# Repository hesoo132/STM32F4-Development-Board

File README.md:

## 📑 Table of Contents
1. [Power](#1-power-전원부)  
2. [Pin Port](#2-pin-port-핀-포트)  
3. [USB](#3-usb)  
4. [Crystal](#4-crystal-크리스탈-오실레이터)  
5. [MCU](#5-mcu-마이크로컨트롤러-유닛)  
6. [Conclusion](#6-결론)  

---

## 1. Power

- **Function**: Converts external 5V input into a regulated 3.3V supply for the MCU and peripherals.  
- **Components**:  
  - AMS1117 regulator (J1)  
  - Power LED (POW_LED_1) with resistor (330Ω)  
  - Slide switch (SW_Slide_DPDT, SW1) for power control  
  - Decoupling capacitors (0.1µF, 10µF) for stability  

---

## 2. Pin Port

- **Function**: Exposes STM32F407VETx GPIOs through external connectors (J3, J4, J5).  
- **Available Pins**:  
  - GPIO groups: PA, PB, PC, PD, PE  
  - Clock pins: OSC_IN, OSC_OUT, OSC32_IN, OSC32_OUT  
  - Reset and Boot pins  
- **Purpose**: Enables flexible interfacing with sensors, actuators, or other controllers.  

---

## 3. USB

- **Function**: Provides USB communication via a Mini-B connector (J2).  
- **Components**:  
  - MIC2025-1YM USB power switch (U1)  
  - Data lines: USB_DP, USB_DM  
  - Protection & series resistors (22Ω)  
  - Power LED (POW_LED2)  
- **Notes**: Supports regulated USB 5V input, current limiting, and device connectivity.  

---

## 4. Crystal

- **Function**: Provides accurate clock sources for the MCU.  
- **Components**:  
  - 8MHz main oscillator (X1) with load capacitors (20pF)  
  - 32.768kHz RTC crystal (Y1) with 6pF capacitors  
  - BOOT Mode selector (J10)  
  - Reset switch (SW2)  
  - 20-pin JTAG/SWD connector (J12) for debugging  

---

## 5. MCU

- **Model**: STM32F407VETx (ARM Cortex-M4)  
- **Function**: Central controller handling all peripherals and system logic.  
- **Connections**:  
  - VCAP capacitors (2.2µF each)  
  - Power pins (3.3V, GND)  
  - BOOT mode jumper (J11)  
  - VBAT connections (J19, J20, J21)  
  - GPIOs (Ports A–E) routed to external headers  
- **Features**:  
  - High-performance MCU core for DSP and control  
  - Rich GPIO set for flexible interfacing  
  - Supports external oscillators and USB  

---

## 6. Conclusion

The **STM32F4Core board** is a versatile core board designed around the STM32F407VETx MCU.  

- **Power Management**: 5V input regulated to 3.3V, with onboard monitoring LEDs and USB power switch.  
- **Expansion**: GPIO-rich design with external pin headers (J3, J4, J5).  
- **USB Support**: Integrated Mini-B port with MIC2025-based power management.  
- **Clock Accuracy**: Dual-crystal design (8MHz + 32.768kHz) ensures reliable MCU timing.  
- **Debugging**: JTAG/SWD interface available for firmware development.  

This makes the board suitable for **embedded system prototyping, robotics, sensor interfacing, and educational use cases** requiring a stable STM32F4 platform.  

---

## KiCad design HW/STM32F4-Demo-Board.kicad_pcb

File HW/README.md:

# STM32F4Core Hardware Design

## 🔎 Overview
The **STM32F4Core Board** is a custom core platform built on the **STM32F407VETx** MCU.  
It provides stable power regulation, rich GPIO breakouts, USB connectivity, accurate system/RTC clocks, and full JTAG/SWD debug support for embedded development.

---

## 📸 PCB Overview
| Top View | Bottom View |
|----------|-------------|
|  |  |

---

## 📑 Design Resources
- **Schematics**: [STM32F4Core.pdf](STM32F4-Demo-Board.pdf) (6-page schematic for quick view)  
- **EDA Tool**: KiCad (v7)  

---

## 🔧 Key Hardware Notes
- **MCU**: STM32F407VETx (ARM Cortex-M4, 168 MHz, FPU)  
- **Power**: 5 V input → AMS1117 regulator → 3.3 V rail, with on/off slide switch & LED indicator  
- **Clocks**: 8 MHz main crystal + 32.768 kHz RTC crystal  
- **USB**: USB Mini-B connector with **MIC2025-1YM** power switch  
- **GPIO**: PA–PE group pins exposed to headers (J3/J4/J5)  
- **Debug**: 20-pin JTAG header (J12), boot-mode jumper (J11), reset switch (SW2)  

---

## 🧩 Schematic Highlights

### 1) Power
  
- **Regulator**: AMS1117 (5 V → 3.3 V)  
- **Indicators**: Power LED (POW_LED_1)  
- **Switch**: Slide switch (SW_Slide_DPDT) for on/off control  

### 2) Pin Ports
  
- **Headers**: J3, J4, J5  
- **Signals**: MCU GPIO (PA/PB/PC/PD/PE), reset, oscillator pins  
- **Use**: Sensor/actuator connections, external module interfacing  

### 3) USB
  
- **Connector**: USB Mini-B (J2)  
- **Power Switch**: MIC2025-1YM, with EN/FLG signals to MCU  
- **Signals**: Provides regulated **USB_5V** rail (with current-limit & flag)  
- **Note**: **Power-only design** — no D+/D− data lines connected to MCU. 

### 4) Clocks & Debug
  
- **Crystals**: 8 MHz (system), 32.768 kHz (RTC)  
- **Reset**: Push switch (SW2)  
- **Debug**: 20-pin JTAG header (J12)  

### 5) MCU
  
- **Chip**: STM32F407VETx  
- **Support**: VCAP capacitors, bypass network, boot-mode jumper (J11)  
- **Role**: Main controller for application logic & peripherals  

---

## ✅ Progress
- [x] Schematics completed (6 pages)  
- [x] PCB prototype fabricated (Rev. A)  
- [x] Power rails validated (5 V → 3.3 V)  
- [x] JTAG/SWD debug verified   
- [x] Full GPIO validation in progress

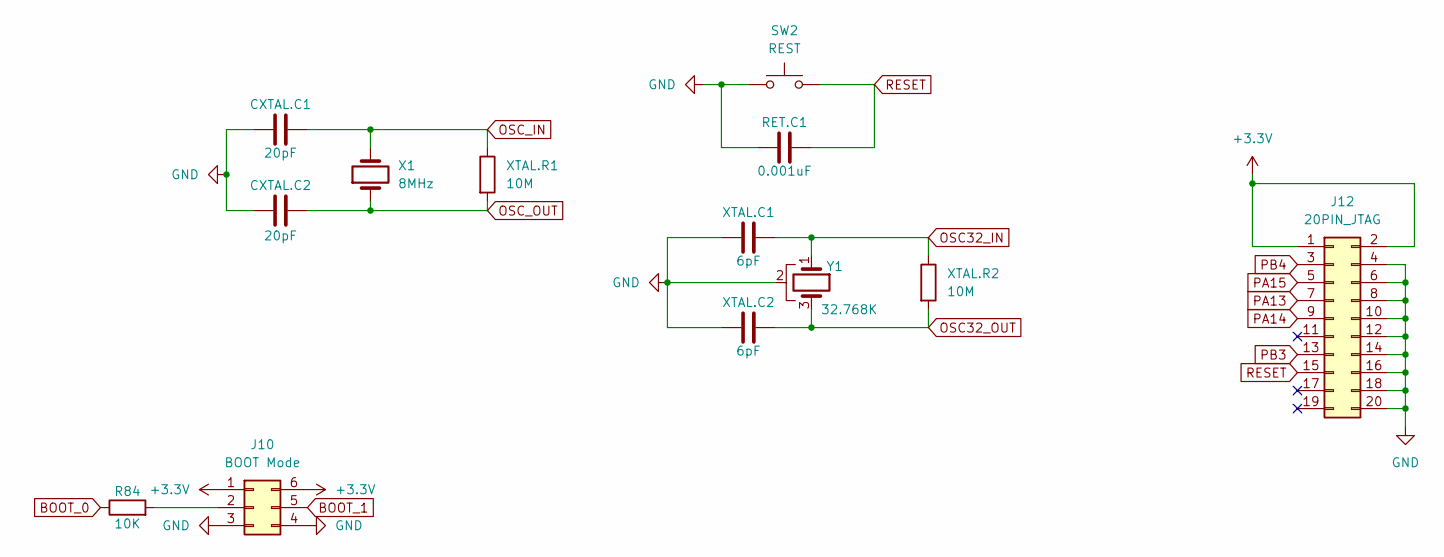
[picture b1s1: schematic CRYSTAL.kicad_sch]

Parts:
CXTAL.C1, CXTAL.C2: 20pF; C_0805_2012Metric
J10: BOOT Mode; PinSocket_2x03_P2.54mm_Vertical
J12: 20PIN_JTAG; IDC-Header_2x10_P2.54mm_Vertical
R84: 10K; C_0805_2012Metric
RET.C1: 0.001uF; C_0805_2012Metric
SW2: REST; SW_MEC_5GSH9
X1: 8MHz; Crystal_HC18-U_Vertical
XTAL.C1, XTAL.C2: 6pF; C_0805_2012Metric
XTAL.R1, XTAL.R2: 10M; R_0805_2012Metric
Y1: 32.768K; Crystal_SMD_MicroCrystal_MS3V-T1R

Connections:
+3.3V: J10.1, J10.6, J12.1, J12.2; also elsewhere on the board
BOOT_0: R84.1; also elsewhere on the board
BOOT_1: J10.5; also elsewhere on the board
GND: CXTAL.C1.1, CXTAL.C2.1, J10.3, J10.4, J12.4, J12.6, J12.8, J12.10, J12.12, J12.14, J12.16, J12.18, J12.20, RET.C1.1, SW2.1 (A), SW2.2 (A), XTAL.C1.1, XTAL.C2.1, Y1.2; also elsewhere on the board
unnamed: J10.2, R84.2
OSC32_IN: XTAL.C1.2, XTAL.R2.1, Y1.1; also elsewhere on the board
OSC32_OUT: XTAL.C2.2, XTAL.R2.2, Y1.3; also elsewhere on the board
OSC_IN: CXTAL.C1.2, X1.2, XTAL.R1.1; also elsewhere on the board
OSC_OUT: CXTAL.C2.2, X1.1, XTAL.R1.2; also elsewhere on the board
PA13: J12.7; also elsewhere on the board
PA14: J12.9; also elsewhere on the board
PA15: J12.5; also elsewhere on the board
PB3: J12.13; also elsewhere on the board
PB4: J12.3; also elsewhere on the board
RESET: J12.15, RET.C1.2, SW2.3 (B), SW2.4 (B); also elsewhere on the board

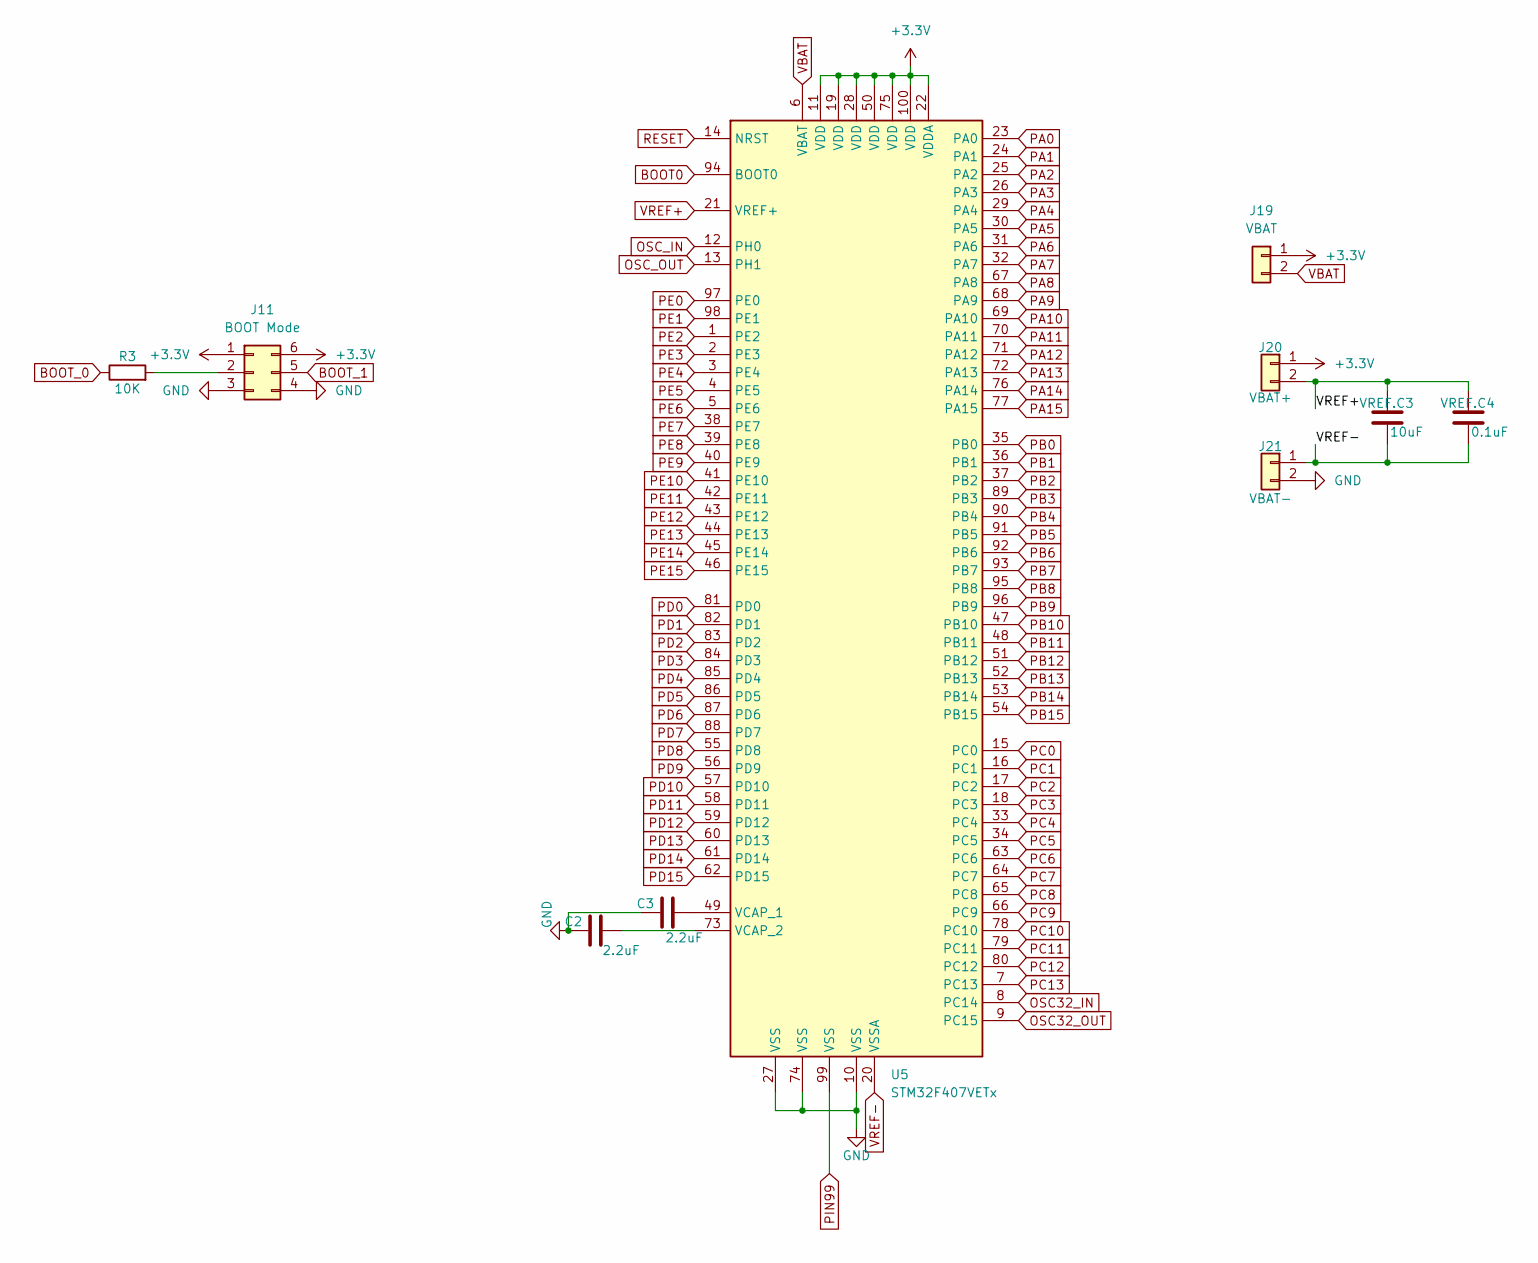
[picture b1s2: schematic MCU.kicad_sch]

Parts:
C2, C3: 2.2uF; C_0805_2012Metric
J11: BOOT Mode; PinSocket_2x03_P2.54mm_Vertical
J19: VBAT; PinHeader_1x02_P2.54mm_Vertical
J20: VBAT+; PinHeader_1x02_P2.54mm_Vertical
J21: VBAT-; PinHeader_1x02_P2.54mm_Vertical
R3: 10K; C_0805_2012Metric
U5: STM32F407VETx; LQFP-100_14x14mm_P0.5mm
VREF.C3: 10uF; C_0805_2012Metric
VREF.C4: 0.1uF; C_0805_2012Metric

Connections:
+3.3V: J11.1, J11.6, J19.1, J20.1, U5.11 (VDD), U5.19 (VDD), U5.22 (VDDA), U5.28 (VDD), U5.50 (VDD), U5.75 (VDD), U5.100 (VDD); also elsewhere on the board
BOOT0: U5.94 (BOOT0); also elsewhere on the board
BOOT_0: R3.1; also elsewhere on the board
BOOT_1: J11.5; also elsewhere on the board
GND: C2.1, C3.1, J11.3, J11.4, J21.2, U5.10 (VSS), U5.27 (VSS), U5.74 (VSS); also elsewhere on the board
unnamed: J11.2, R3.2
unnamed: C3.2, U5.49 (VCAP_1)
unnamed: C2.2, U5.73 (VCAP_2)
OSC32_IN: U5.8 (PC14); also elsewhere on the board
OSC32_OUT: U5.9 (PC15); also elsewhere on the board
OSC_IN: U5.12 (PH0); also elsewhere on the board
OSC_OUT: U5.13 (PH1); also elsewhere on the board
PA0: U5.23 (PA0); also elsewhere on the board
PA1: U5.24 (PA1); also elsewhere on the board
PA2: U5.25 (PA2); also elsewhere on the board
PA3: U5.26 (PA3); also elsewhere on the board
PA4: U5.29 (PA4); also elsewhere on the board
PA5: U5.30 (PA5); also elsewhere on the board
PA6: U5.31 (PA6); also elsewhere on the board
PA7: U5.32 (PA7); also elsewhere on the board
PA8: U5.67 (PA8); also elsewhere on the board
PA9: U5.68 (PA9); also elsewhere on the board
PA10: U5.69 (PA10); also elsewhere on the board
PA11: U5.70 (PA11); also elsewhere on the board
PA12: U5.71 (PA12); also elsewhere on the board
PA13: U5.72 (PA13); also elsewhere on the board
PA14: U5.76 (PA14); also elsewhere on the board
PA15: U5.77 (PA15); also elsewhere on the board
PB0: U5.35 (PB0); also elsewhere on the board
PB1: U5.36 (PB1); also elsewhere on the board
PB2: U5.37 (PB2); also elsewhere on the board
PB3: U5.89 (PB3); also elsewhere on the board
PB4: U5.90 (PB4); also elsewhere on the board
PB5: U5.91 (PB5); also elsewhere on the board
PB6: U5.92 (PB6); also elsewhere on the board
PB7: U5.93 (PB7); also elsewhere on the board
PB8: U5.95 (PB8); also elsewhere on the board
PB9: U5.96 (PB9); also elsewhere on the board
PB10: U5.47 (PB10); also elsewhere on the board
PB11: U5.48 (PB11); also elsewhere on the board
PB12: U5.51 (PB12); also elsewhere on the board
PB13: U5.52 (PB13); also elsewhere on the board
PB14: U5.53 (PB14); also elsewhere on the board
PB15: U5.54 (PB15); also elsewhere on the board
PC0: U5.15 (PC0); also elsewhere on the board
PC1: U5.16 (PC1); also elsewhere on the board
PC2: U5.17 (PC2); also elsewhere on the board
PC3: U5.18 (PC3); also elsewhere on the board
PC4: U5.33 (PC4); also elsewhere on the board
PC5: U5.34 (PC5); also elsewhere on the board
PC6: U5.63 (PC6); also elsewhere on the board
PC7: U5.64 (PC7); also elsewhere on the board
PC8: U5.65 (PC8); also elsewhere on the board
PC9: U5.66 (PC9); also elsewhere on the board
PC10: U5.78 (PC10); also elsewhere on the board
PC11: U5.79 (PC11); also elsewhere on the board
PC12: U5.80 (PC12); also elsewhere on the board
PC13: U5.7 (PC13); also elsewhere on the board
PD0: U5.81 (PD0); also elsewhere on the board
PD1: U5.82 (PD1); also elsewhere on the board
PD2: U5.83 (PD2); also elsewhere on the board
PD3: U5.84 (PD3); also elsewhere on the board
PD4: U5.85 (PD4); also elsewhere on the board
PD5: U5.86 (PD5); also elsewhere on the board
PD6: U5.87 (PD6); also elsewhere on the board
PD7: U5.88 (PD7); also elsewhere on the board
PD8: U5.55 (PD8); also elsewhere on the board
PD9: U5.56 (PD9); also elsewhere on the board
PD10: U5.57 (PD10); also elsewhere on the board
PD11: U5.58 (PD11); also elsewhere on the board
PD12: U5.59 (PD12); also elsewhere on the board
PD13: U5.60 (PD13); also elsewhere on the board
PD14: U5.61 (PD14); also elsewhere on the board
PD15: U5.62 (PD15); also elsewhere on the board
PE0: U5.97 (PE0); also elsewhere on the board
PE1: U5.98 (PE1); also elsewhere on the board
PE2: U5.1 (PE2); also elsewhere on the board
PE3: U5.2 (PE3); also elsewhere on the board
PE4: U5.3 (PE4); also elsewhere on the board
PE5: U5.4 (PE5); also elsewhere on the board
PE6: U5.5 (PE6); also elsewhere on the board
PE7: U5.38 (PE7); also elsewhere on the board
PE8: U5.39 (PE8); also elsewhere on the board
PE9: U5.40 (PE9); also elsewhere on the board
PE10: U5.41 (PE10); also elsewhere on the board
PE11: U5.42 (PE11); also elsewhere on the board
PE12: U5.43 (PE12); also elsewhere on the board
PE13: U5.44 (PE13); also elsewhere on the board
PE14: U5.45 (PE14); also elsewhere on the board
PE15: U5.46 (PE15); also elsewhere on the board
PIN99: U5.99 (VSS)
RESET: U5.14 (NRST); also elsewhere on the board
VBAT: J19.2, U5.6 (VBAT); also elsewhere on the board
VREF+: J20.2, U5.21 (VREF+), VREF.C3.1, VREF.C4.1; also elsewhere on the board
VREF-: J21.1, U5.20 (VSSA), VREF.C3.2, VREF.C4.2; also elsewhere on the board

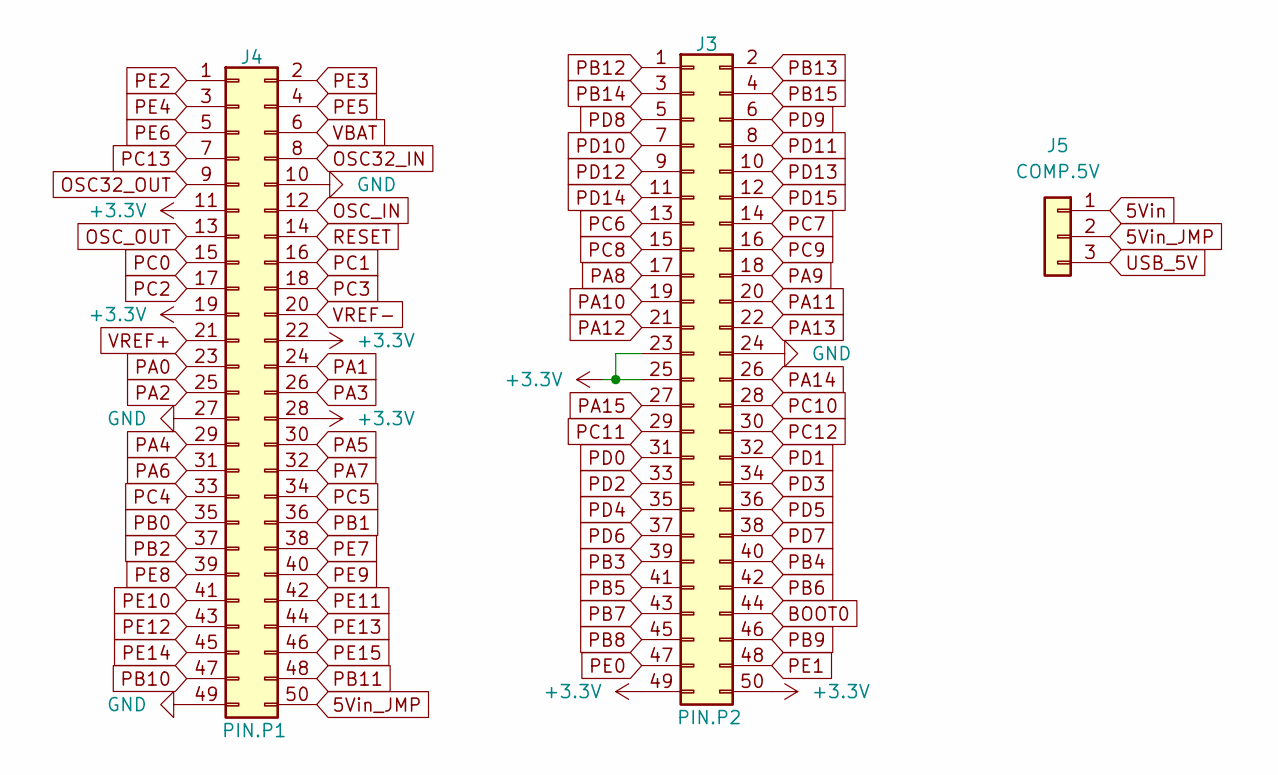
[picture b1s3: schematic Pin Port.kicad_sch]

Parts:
J3: PIN.P2; PinHeader_2x25_P2.54mm_Vertical
J4: PIN.P1; PinHeader_2x25_P2.54mm_Vertical
J5: COMP.5V; SolderJumper-3_P1.3mm_Open_Pad1.0x1.5mm

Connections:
5Vin: J5.1; also elsewhere on the board
5Vin_JMP: J4.50, J5.2
+3.3V: J3.23, J3.25, J3.49, J3.50, J4.11, J4.19, J4.22, J4.28; also elsewhere on the board
BOOT0: J3.44; also elsewhere on the board
GND: J3.24, J4.10, J4.27, J4.49; also elsewhere on the board
OSC32_IN: J4.8; also elsewhere on the board
OSC32_OUT: J4.9; also elsewhere on the board
OSC_IN: J4.12; also elsewhere on the board
OSC_OUT: J4.13; also elsewhere on the board
PA0: J4.23; also elsewhere on the board
PA1: J4.24; also elsewhere on the board
PA2: J4.25; also elsewhere on the board
PA3: J4.26; also elsewhere on the board
PA4: J4.29; also elsewhere on the board
PA5: J4.30; also elsewhere on the board
PA6: J4.31; also elsewhere on the board
PA7: J4.32; also elsewhere on the board
PA8: J3.17; also elsewhere on the board
PA9: J3.18; also elsewhere on the board
PA10: J3.19; also elsewhere on the board
PA11: J3.20; also elsewhere on the board
PA12: J3.21; also elsewhere on the board
PA13: J3.22; also elsewhere on the board
PA14: J3.26; also elsewhere on the board
PA15: J3.27; also elsewhere on the board
PB0: J4.35; also elsewhere on the board
PB1: J4.36; also elsewhere on the board
PB2: J4.37; also elsewhere on the board
PB3: J3.39; also elsewhere on the board
PB4: J3.40; also elsewhere on the board
PB5: J3.41; also elsewhere on the board
PB6: J3.42; also elsewhere on the board
PB7: J3.43; also elsewhere on the board
PB8: J3.45; also elsewhere on the board
PB9: J3.46; also elsewhere on the board
PB10: J4.47; also elsewhere on the board
PB11: J4.48; also elsewhere on the board
PB12: J3.1; also elsewhere on the board
PB13: J3.2; also elsewhere on the board
PB14: J3.3; also elsewhere on the board
PB15: J3.4; also elsewhere on the board
PC0: J4.15; also elsewhere on the board
PC1: J4.16; also elsewhere on the board
PC2: J4.17; also elsewhere on the board
PC3: J4.18; also elsewhere on the board
PC4: J4.33; also elsewhere on the board
PC5: J4.34; also elsewhere on the board
PC6: J3.13; also elsewhere on the board
PC7: J3.14; also elsewhere on the board
PC8: J3.15; also elsewhere on the board
PC9: J3.16; also elsewhere on the board
PC10: J3.28; also elsewhere on the board
PC11: J3.29; also elsewhere on the board
PC12: J3.30; also elsewhere on the board
PC13: J4.7; also elsewhere on the board
PD0: J3.31; also elsewhere on the board
PD1: J3.32; also elsewhere on the board
PD2: J3.33; also elsewhere on the board
PD3: J3.34; also elsewhere on the board
PD4: J3.35; also elsewhere on the board
PD5: J3.36; also elsewhere on the board
PD6: J3.37; also elsewhere on the board
PD7: J3.38; also elsewhere on the board
PD8: J3.5; also elsewhere on the board
PD9: J3.6; also elsewhere on the board
PD10: J3.7; also elsewhere on the board
PD11: J3.8; also elsewhere on the board
PD12: J3.9; also elsewhere on the board
PD13: J3.10; also elsewhere on the board
PD14: J3.11; also elsewhere on the board
PD15: J3.12; also elsewhere on the board
PE0: J3.47; also elsewhere on the board
PE1: J3.48; also elsewhere on the board
PE2: J4.1; also elsewhere on the board
PE3: J4.2; also elsewhere on the board
PE4: J4.3; also elsewhere on the board
PE5: J4.4; also elsewhere on the board
PE6: J4.5; also elsewhere on the board
PE7: J4.38; also elsewhere on the board
PE8: J4.39; also elsewhere on the board
PE9: J4.40; also elsewhere on the board
PE10: J4.41; also elsewhere on the board
PE11: J4.42; also elsewhere on the board
PE12: J4.43; also elsewhere on the board
PE13: J4.44; also elsewhere on the board
PE14: J4.45; also elsewhere on the board
PE15: J4.46; also elsewhere on the board
RESET: J4.14; also elsewhere on the board
USB_5V: J5.3; also elsewhere on the board
VBAT: J4.6; also elsewhere on the board
VREF+: J4.21; also elsewhere on the board
VREF-: J4.20; also elsewhere on the board

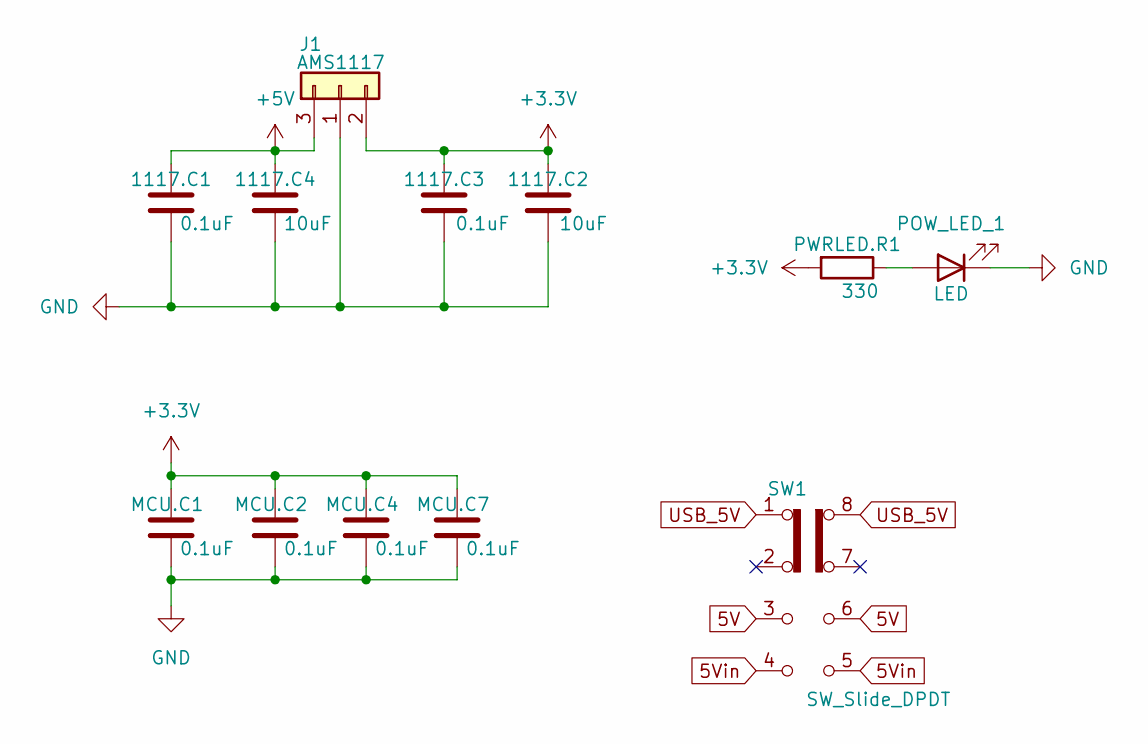
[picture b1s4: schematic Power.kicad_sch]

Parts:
1117.C1, 1117.C3: 0.1uF; C_0805_2012Metric
1117.C2, 1117.C4: 10uF; C_0805_2012Metric
J1: AMS1117; FanPinHeader_1x03_P2.54mm_Vertical
MCU.C1, MCU.C2, MCU.C4, MCU.C7: 0.1uF; C_0805_2012Metric
POW_LED_1: LED; LED_0805_2012Metric
PWRLED.R1: 330; R_0805_2012Metric
SW1: SW_Slide_DPDT; MY_SW

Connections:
5V: SW1.3 (C), SW1.6 (A)
5Vin: SW1.4, SW1.5; also elsewhere on the board
+3.3V: 1117.C2.1, 1117.C3.1, J1.2, MCU.C1.1, MCU.C2.1, MCU.C4.1, MCU.C7.1, PWRLED.R1.2; also elsewhere on the board
+5V: 1117.C1.1, 1117.C4.1, J1.3
GND: 1117.C1.2, 1117.C2.2, 1117.C3.2, 1117.C4.2, J1.1, MCU.C1.2, MCU.C2.2, MCU.C4.2, MCU.C7.2, POW_LED_1.1 (K); also elsewhere on the board
unnamed: POW_LED_1.2 (A), PWRLED.R1.1
USB_5V: SW1.1 (A), SW1.8 (C); also elsewhere on the board

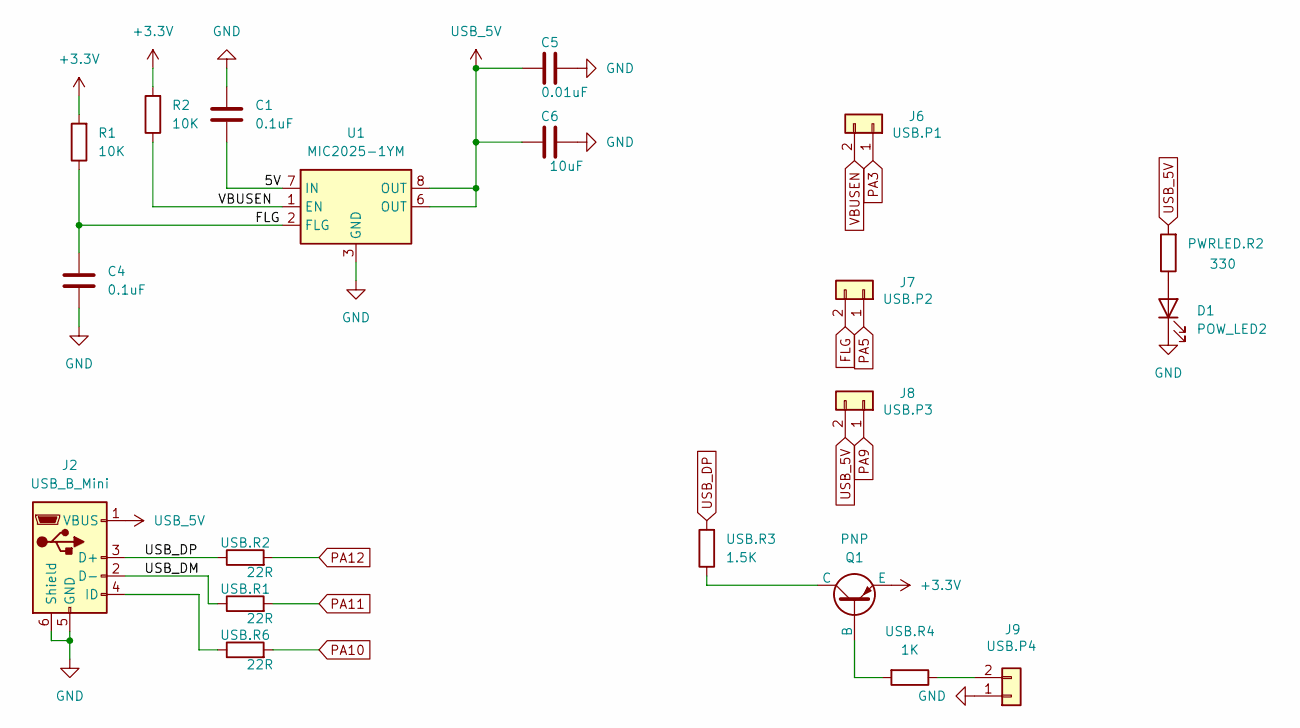
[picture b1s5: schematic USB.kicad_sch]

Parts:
C1, C4: 0.1uF; C_0805_2012Metric
C5: 0.01uF; C_0805_2012Metric
C6: 10uF; C_0805_2012Metric
D1: POW_LED2; LED_0805_2012Metric
J2: USB_B_Mini; USB_Mini-B_Wuerth_65100516121_Horizontal
J6: USB.P1; PinHeader_1x02_P2.54mm_Vertical
J7: USB.P2; PinHeader_1x02_P2.54mm_Vertical
J8: USB.P3; PinHeader_1x02_P2.54mm_Vertical
J9: USB.P4; PinHeader_1x02_P2.54mm_Vertical
PWRLED.R2: 330; R_0805_2012Metric
Q1: PNP; SOT-23-3
R1, R2: 10K; C_0805_2012Metric
U1: MIC2025-1YM; SOIC-8_3.9x4.9mm_P1.27mm
USB.R1, USB.R2, USB.R6: 22R; R_0805_2012Metric
USB.R3: 1.5K; R_0805_2012Metric
USB.R4: 1K; R_0805_2012Metric

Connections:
+3.3V: Q1.3 (E), R1.2, R2.2; also elsewhere on the board
/USB/5V: C1.2, U1.7 (IN)
/USB/USB_DM: J2.2 (D-), USB.R1.1
FLG: C4.1, J7.2, R1.1, U1.2 (FLG)
GND: C1.1, C4.2, C5.2, C6.2, D1.1 (K), J2.5 (GND), J2.6 (Shield), J9.1, U1.3 (GND); also elsewhere on the board
unnamed: D1.2 (A), PWRLED.R2.1
unnamed: J2.4 (ID), USB.R6.1
unnamed: J9.2, USB.R4.1
unnamed: Q1.2 (B), USB.R4.2
unnamed: Q1.1 (C), USB.R3.1
PA3: J6.1; also elsewhere on the board
PA5: J7.1; also elsewhere on the board
PA9: J8.1; also elsewhere on the board
PA10: USB.R6.2; also elsewhere on the board
PA11: USB.R1.2; also elsewhere on the board
PA12: USB.R2.2; also elsewhere on the board
USB_5V: C5.1, C6.1, J2.1 (VBUS), J8.2, PWRLED.R2.2, U1.6 (OUT), U1.8 (OUT); also elsewhere on the board
USB_DP: J2.3 (D+), USB.R2.1, USB.R3.2
VBUSEN: J6.2, R2.1, U1.1 (EN)

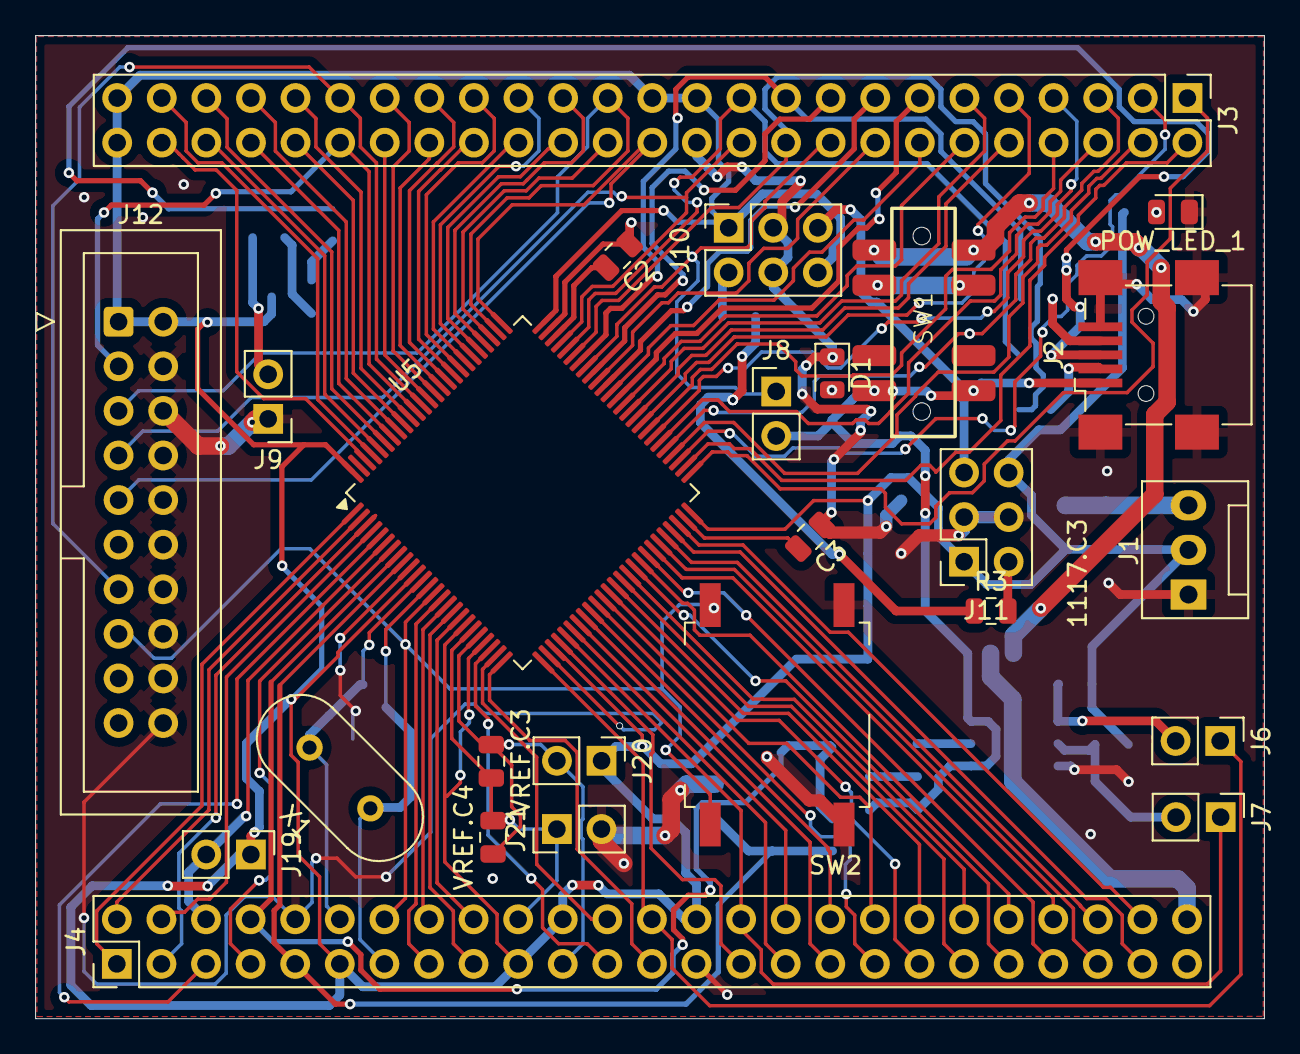
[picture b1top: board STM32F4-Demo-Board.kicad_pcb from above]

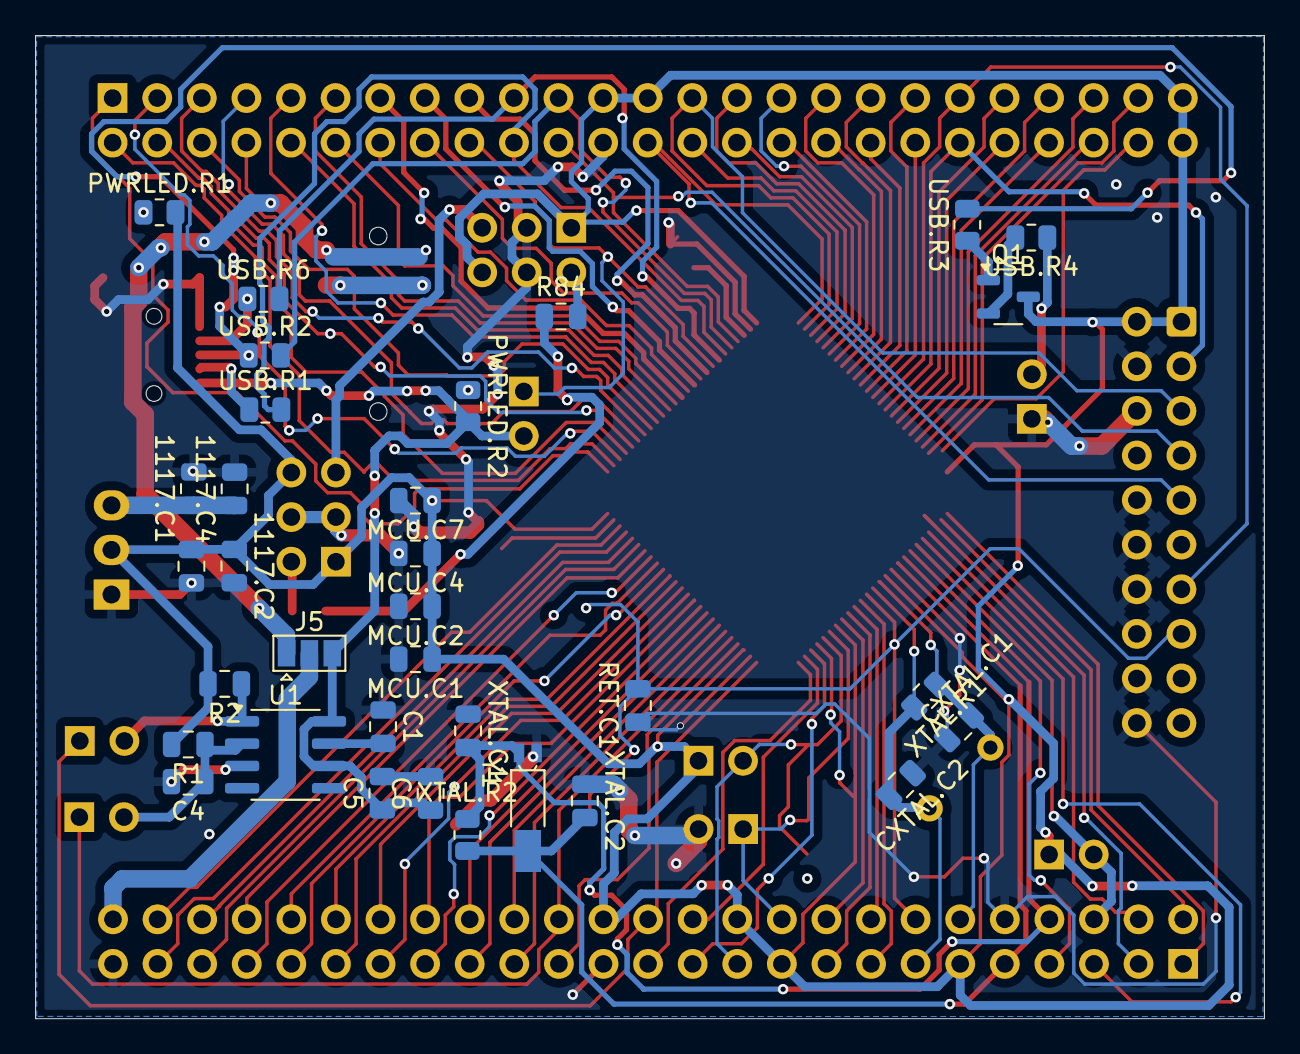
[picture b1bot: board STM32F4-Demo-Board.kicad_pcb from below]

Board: 2 copper layers, 70.0 x 56.0 mm, 58 parts (33 on the bottom side), 111 nets.

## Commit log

2025-08-23 README.md
